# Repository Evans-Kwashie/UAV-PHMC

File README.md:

# UAV-PHMC
### UAV Power, Hardware & Motor Controller

UAV-PHMC is an embedded hardware development project focused on designing a custom printed circuit board (PCB) for UAV control and power-management applications.

The project brings together power regulation, hardware interfaces, monitoring circuitry, and embedded-system integration on a custom four-layer PCB.

The repository contains the KiCad hardware design files alongside manufacturing outputs for PCB fabrication and assembly.

---

## Project Overview

The UAV-PHMC board is designed around the **STM32G071KBUx** microcontroller and provides the hardware foundation for interfacing with UAV subsystems.

Key design areas include:

- Custom four-layer PCB design.
- STM32G071KBUx microcontroller integration.
- Multi-rail power distribution.
- Voltage and current monitoring.
- Protected GPIO interfaces.
- Communication interfaces for external peripherals.
- PCB fabrication and assembly preparation.

## Hardware Features

| Feature | Description |
|---|---|
| Microcontroller | STM32G071KBUx |
| PCB | Custom four-layer design |
| Power regulation | TPS562202S-based regulation |
| Current monitoring | INA226 |
| Power rails | VBAT_RAW, 5V, 5V_CAM, 3V3 |
| Communication | UART, I²C, RS-485 |
| GPIO | Protected external GPIO interfaces |
| Design software | KiCad |

## Power Architecture

The hardware design incorporates multiple power domains to support the board and its connected peripherals.

| Power net | Purpose |
|---|---|
| VBAT_RAW | Raw battery input |
| 5V | Main regulated 5V supply |
| 5V_CAM | Camera power supply |
| 3V3 | Logic and microcontroller supply |

The design includes voltage and current monitoring using the INA226, supporting power-system observation and integration.

## Repository Structure

```text
UAV-PHMC/
│
├── hardware/
│   ├── bom/
│   │   └── hardware.csv
│   │
│   ├── gerbers/
│   │   ├── PHMC_gerbers.zip
│   │   ├── hardware-Front.gtl
│   │   ├── hardware-Back.gbl
│   │   ├── hardware-Edge_Cuts.gm1
│   │   └── ... fabrication layers and drill files
│   │
│   ├── pick_place/
│   │   └── hardware-all.pos
│   │
│   ├── hardware.kicad_pcb
│   ├── hardware.kicad_pro
│   └── hardware.glb
│
├── .gitignore
└── README.md
```

## Manufacturing Outputs

The repository includes the following manufacturing-related files:

**Bill of Materials (BOM)**
- `hardware/bom/hardware.csv`

**Gerber and Drill Files**
- `hardware/gerbers/`

**Pick-and-Place Data**
- `hardware/pick_place/hardware-all.pos`

**3D PCB Model**
- `hardware/hardware.glb`

**Gerber Archive**
- `hardware/gerbers/PHMC_gerbers.zip`

These files are provided to support PCB fabrication, component sourcing, assembly preparation, and design review.

Before manufacturing, verify that the Gerber outputs, drill files, BOM, and pick-and-place data correspond to the intended PCB revision.

## Opening the Hardware Design

1. Install [KiCad](https://www.kicad.org/).
2. Clone or download this repository.
3. Navigate to the `hardware/` directory.
4. Open `hardware.kicad_pro` in KiCad.
5. Inspect the schematic and PCB design as applicable.

The 3D model can also be inspected using a compatible 3D viewer.

## Project Status

**Hardware design and manufacturing outputs committed.**

The repository currently includes the PCB design, project configuration, BOM, Gerber fabrication files, drill data, pick-and-place coordinates, and 3D model.

The inclusion of manufacturing outputs does not imply that the board has been fabricated, assembled, electrically validated, or flight-tested.

## Tools & Technologies

- **KiCad** — PCB design and layout.
- **STM32** — Embedded microcontroller platform.
- **INA226** — Voltage and current monitoring.
- **TPS562202S** — Power regulation.
- **Gerber** — PCB fabrication data.
- **3D CAD** — PCB visualization and mechanical inspection.

## Licensing

### Hardware design

The hardware design files in this repository, including schematics, PCB layouts, manufacturing outputs and related hardware documentation, are licensed under the **CERN Open Hardware Licence Version 2 – Strongly Reciprocal (CERN-OHL-S-2.0)**. See [LICENSE](./LICENSE).

The complete source for this hardware design is available in this repository: https://github.com/Evans-Kwashie/UAV-PHMC

### Software

Any firmware, software or code in this repository that is explicitly identified as software is licensed under the **MIT License**. See [LICENSE-MIT](./LICENSE-MIT). Third-party components remain under their respective licences.

## Author

**Evans Klenam Kwashie-Seyram**

- GitHub: [@Evans-Kwashie](https://github.com/Evans-Kwashie)
- LinkedIn: [Evans Klenam Kwashie-Seyram](https://linkedin.com/in/evans-klenam-kwashie-seyram)
- Portfolio: [pcb-portfolio.vercel.app](https://pcb-portfolio.vercel.app)

---

*UAV-PHMC — Custom embedded hardware for UAV systems.*

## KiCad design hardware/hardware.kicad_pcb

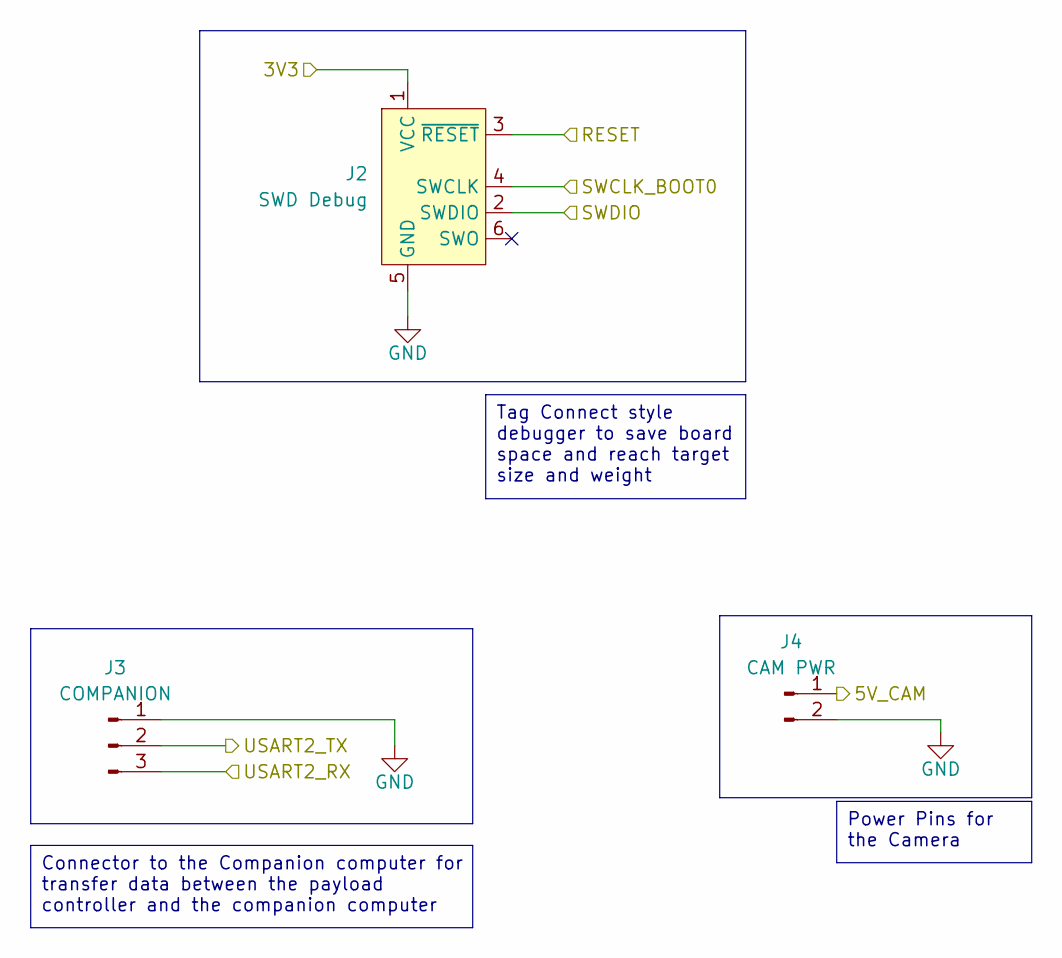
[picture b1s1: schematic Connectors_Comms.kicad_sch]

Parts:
J2: SWD Debug; Tag-Connect_TC2030-IDC-NL_2x03_P1.27mm_Vertical
J3: COMPANION; JST_SH_SM03B-SRSS-TB_1x03-1MP_P1.00mm_Horizontal
J4: CAM PWR; JST_SH_SM02B-SRSS-TB_1x02-1MP_P1.00mm_Horizontal

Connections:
/Connectors_Comms/3V3: J2.1 (VCC); also elsewhere on the board
/Connectors_Comms/5V_CAM: J4.1; also elsewhere on the board
/Connectors_Comms/RESET: J2.3 (~RESET); also elsewhere on the board
/Connectors_Comms/SWCLK_BOOT0: J2.4 (SWCLK); also elsewhere on the board
/Connectors_Comms/SWDIO: J2.2 (SWDIO); also elsewhere on the board
/Connectors_Comms/USART2_RX: J3.3; also elsewhere on the board
/Connectors_Comms/USART2_TX: J3.2; also elsewhere on the board
GND: J2.5 (GND), J3.1, J4.2; also elsewhere on the board

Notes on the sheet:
Tag Connect style debugger to save board space and reach target size and weight
Power Pins for the Camera
Connector to the Companion computer for transfer data between the payload controller and the companion computer

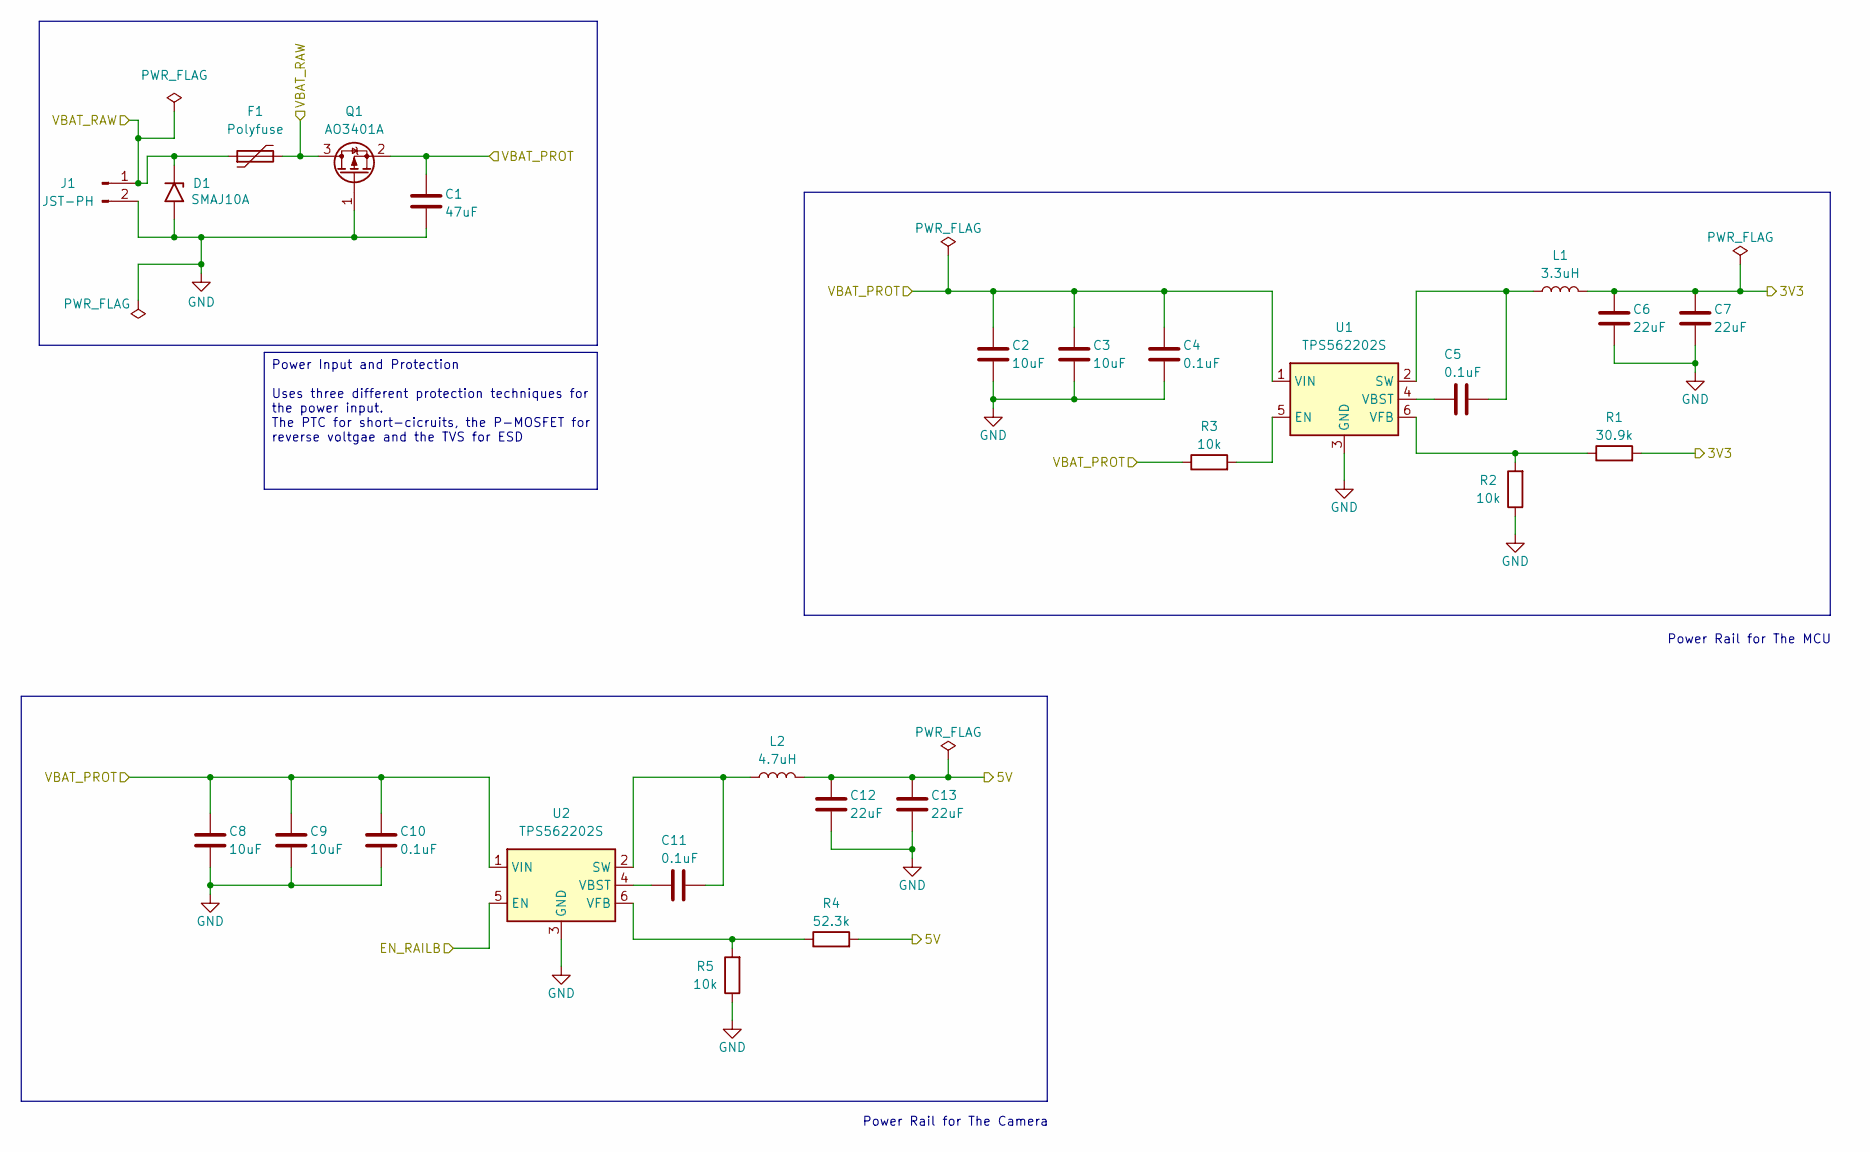
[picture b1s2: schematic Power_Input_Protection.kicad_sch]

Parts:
C1: 47uF; C_1210_3225Metric
C2, C3, C8, C9: 10uF; C_0805_2012Metric
C4, C5, C10, C11: 0.1uF; C_0603_1608Metric
C6, C7, C12, C13: 22uF; C_1206_3216Metric
D1: SMAJ10A; D_SMA
F1: Polyfuse; F_1812_4532Metric
J1: JST-PH; JST_PH_S2B-PH-SM4-TB_1x02-1MP_P2.00mm_Horizontal
L1: 3.3uH; L_Coilcraft_XFL2010
L2: 4.7uH; L_Coilcraft_XAL4020-XXX
Q1: AO3401A; SOT-23
R1: 30.9k; R_0201_0603Metric
R2, R3, R5: 10k; R_0201_0603Metric
R4: 52.3k; R_0201_0603Metric
U1, U2: TPS562202S; SOT-563

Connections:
/Connectors_Comms/3V3: C6.1, C7.1, L1.2, R1.2; also elsewhere on the board
/Current_Sense/5V: C12.1, C13.1, L2.2, R4.2; also elsewhere on the board
/Current_Sense/VBAT_PROT: C1.1, C2.1, C3.1, C4.1, C8.1, C9.1, C10.1, Q1.2 (S), R3.1, U1.1 (VIN), U2.1 (VIN); also elsewhere on the board
/Current_Sense/VBAT_RAW: D1.1 (A1), F1.1, F1.2, J1.1, Q1.3 (D); also elsewhere on the board
/MCU/EN_RAILB: U2.5 (EN); also elsewhere on the board
GND: C1.2, C2.2, C3.2, C4.2, C6.2, C7.2, C8.2, C9.2, C10.2, C12.2, C13.2, D1.2 (A2), J1.2, Q1.1 (G), R2.1, R5.1, U1.3 (GND), U2.3 (GND); also elsewhere on the board
unnamed: R3.2, U1.5 (EN)
unnamed: C5.2, L1.1, U1.2 (SW)
unnamed: C5.1, U1.4 (VBST)
unnamed: R1.1, R2.2, U1.6 (VFB)
unnamed: C11.2, L2.1, U2.2 (SW)
unnamed: C11.1, U2.4 (VBST)
unnamed: R4.1, R5.2, U2.6 (VFB)

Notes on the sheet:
Power Rail for The Camera
Power Rail for The MCU
Power Input and Protection Uses three different protection techniques for the power input. The PTC for short-cicruits, the P-MOSFET for reverse voltgae and the TVS for ESD

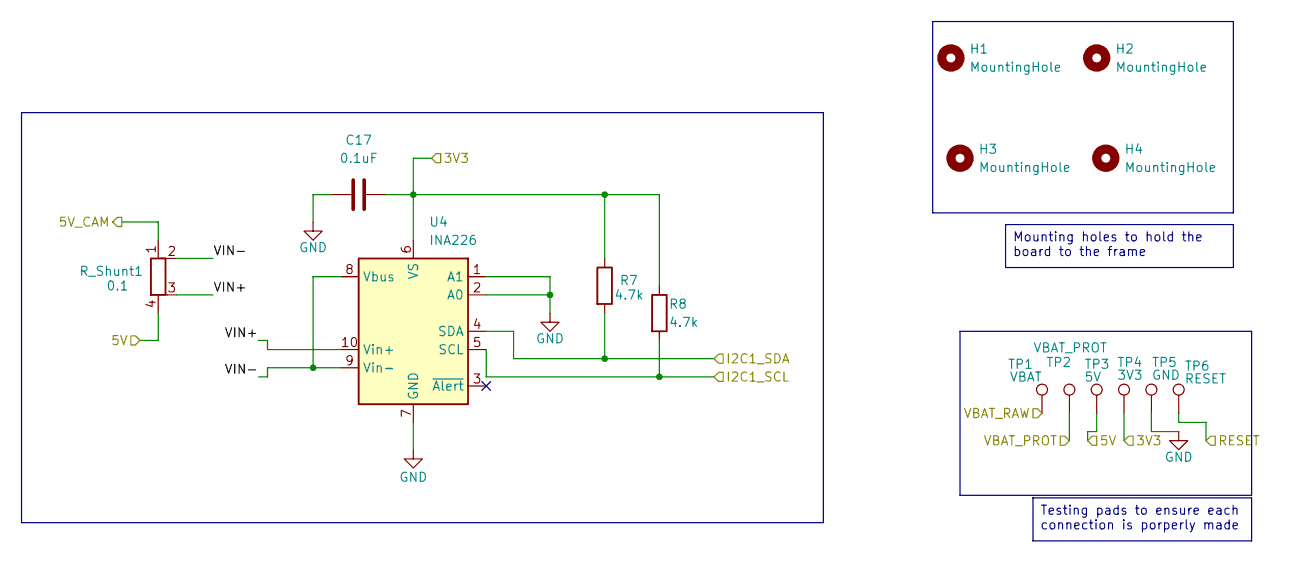
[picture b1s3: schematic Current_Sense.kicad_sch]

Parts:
C17: 0.1uF; C_0603_1608Metric
H1, H2, H3, H4: MountingHole; MountingHole_2.2mm_M2
R7, R8: 4.7k; R_0201_0603Metric
R_Shunt1: 0.1; R_Shunt_Vishay_WSK2512_6332Metric_T2.21mm
TP1: VBAT; TestPoint_Pad_D1.0mm
TP2: VBAT_PROT; TestPoint_Pad_D1.0mm
TP3: 5V; TestPoint_Pad_D1.0mm
TP4: 3V3; TestPoint_Pad_D1.0mm
TP5: GND; TestPoint_Pad_D1.0mm
TP6: RESET; TestPoint_Pad_D1.0mm
U4: INA226; TSSOP-10_3x3mm_P0.5mm

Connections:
/Connectors_Comms/3V3: C17.2, R7.1, R8.1, TP4.1 (1_1), U4.6 (VS); also elsewhere on the board
/Connectors_Comms/5V_CAM: R_Shunt1.1; also elsewhere on the board
/Connectors_Comms/RESET: TP6.1 (1_1); also elsewhere on the board
/Current_Sense/5V: R_Shunt1.4, TP3.1 (1_1); also elsewhere on the board
/Current_Sense/I2C1_SCL: R8.2, U4.5 (SCL); also elsewhere on the board
/Current_Sense/I2C1_SDA: R7.2, U4.4 (SDA); also elsewhere on the board
/Current_Sense/VBAT_PROT: TP2.1 (1_1); also elsewhere on the board
/Current_Sense/VBAT_RAW: TP1.1 (1_1); also elsewhere on the board
/Current_Sense/VIN+: R_Shunt1.3, U4.10 (Vin+)
/Current_Sense/VIN-: R_Shunt1.2, U4.8 (Vbus), U4.9 (Vin-)
GND: C17.1, TP5.1 (1_1), U4.1 (A1), U4.2 (A0), U4.7 (GND); also elsewhere on the board

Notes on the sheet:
Testing pads to ensure each connection is porperly made
Mounting holes to hold the board to the frame

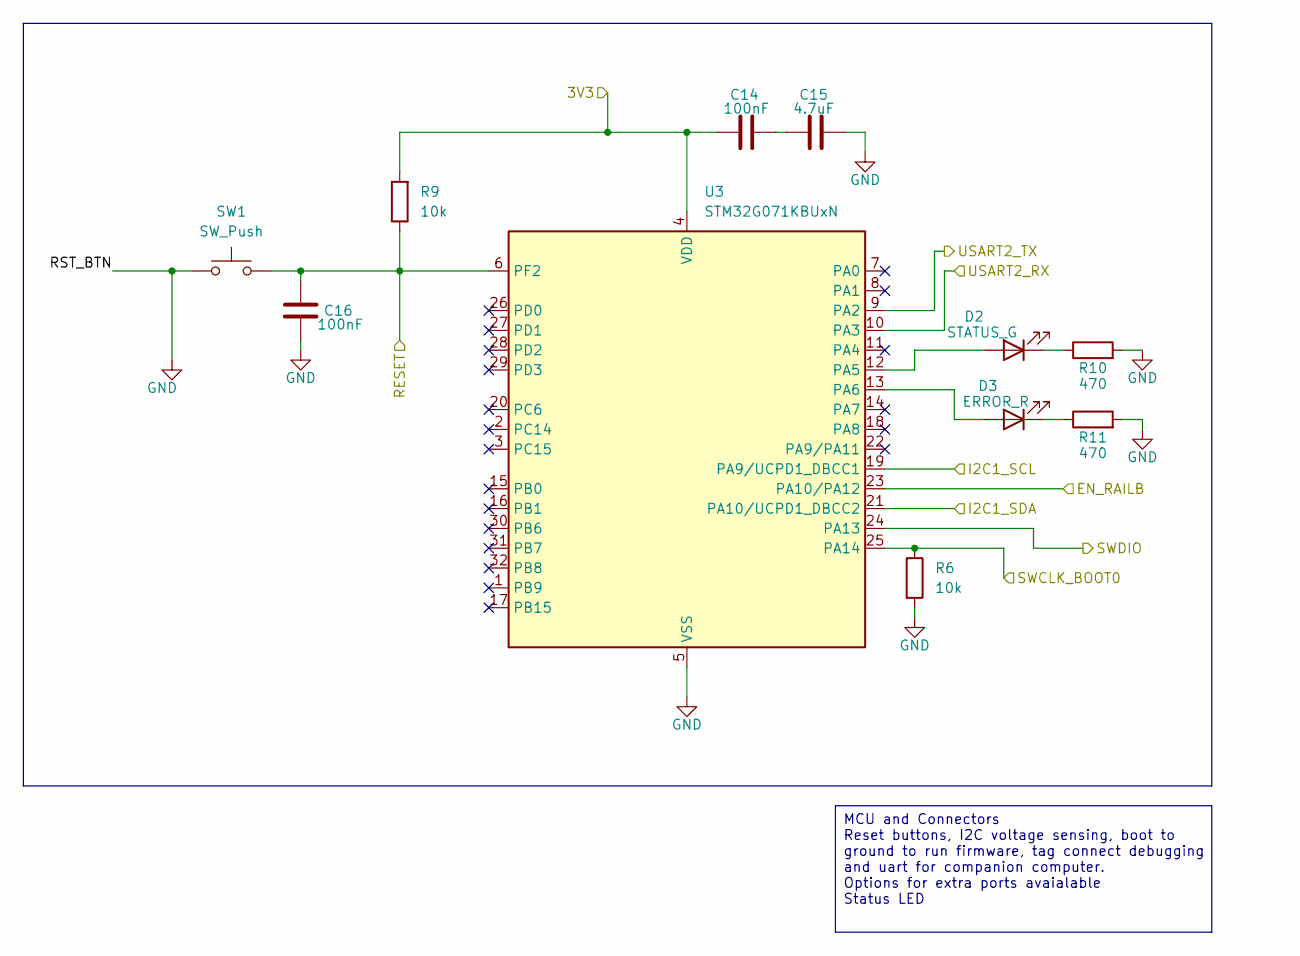
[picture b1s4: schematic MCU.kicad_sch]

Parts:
C14, C16: 100nF; C_0603_1608Metric
C15: 4.7uF; C_0603_1608Metric
D2: STATUS_G; LED_0201_0603Metric
D3: ERROR_R; LED_0201_0603Metric
R6, R9: 10k; R_0201_0603Metric
R10, R11: 470; R_0201_0603Metric
SW1: SW_Push; SW_SPST_EVQP2_MiddlePushTravel_H2.5mm
U3: STM32G071KBUxN; QFN-32-1EP_5x5mm_P0.5mm_EP3.45x3.45mm

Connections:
/Connectors_Comms/3V3: C14.1, R9.2, U3.4 (VDD); also elsewhere on the board
/Connectors_Comms/RESET: C16.1, R9.1, SW1.2, U3.6 (PF2); also elsewhere on the board
/Connectors_Comms/SWCLK_BOOT0: R6.1, U3.25 (PA14); also elsewhere on the board
/Connectors_Comms/SWDIO: U3.24 (PA13); also elsewhere on the board
/Connectors_Comms/USART2_RX: U3.10 (PA3); also elsewhere on the board
/Connectors_Comms/USART2_TX: U3.9 (PA2); also elsewhere on the board
/Current_Sense/I2C1_SCL: U3.19 (PA9/UCPD1_DBCC1); also elsewhere on the board
/Current_Sense/I2C1_SDA: U3.21 (PA10/UCPD1_DBCC2); also elsewhere on the board
/MCU/EN_RAILB: U3.23 (PA10/PA12); also elsewhere on the board
GND: C15.2, C16.2, R6.2, R10.2, R11.2, SW1.1, U3.5 (VSS), U3.33 (VSS); also elsewhere on the board
unnamed: C14.2, C15.1
unnamed: D2.2 (A), U3.12 (PA5)
unnamed: D2.1 (K), R10.1
unnamed: D3.2 (A), U3.13 (PA6)
unnamed: D3.1 (K), R11.1

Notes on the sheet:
MCU and Connectors Reset buttons, I2C voltage sensing, boot to ground to run firmware, tag connect debugging and uart for companion computer. Options for extra ports avaialable Status LED

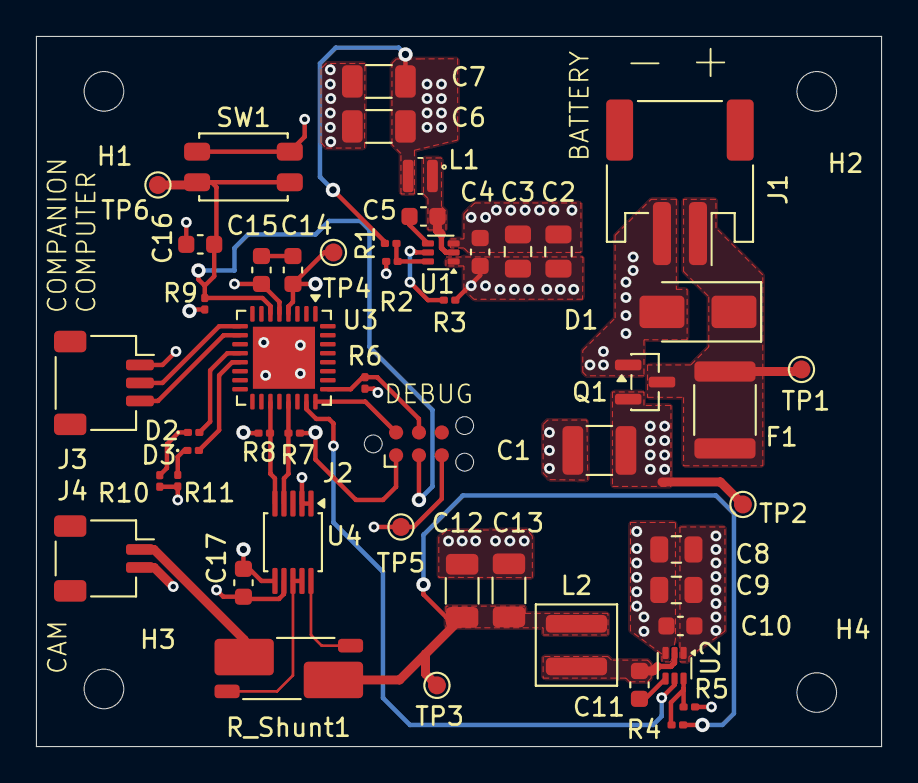
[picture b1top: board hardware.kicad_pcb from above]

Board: 4 copper layers, 46.9 x 39.5 mm, 55 parts (0 on the bottom side), 28 nets.
